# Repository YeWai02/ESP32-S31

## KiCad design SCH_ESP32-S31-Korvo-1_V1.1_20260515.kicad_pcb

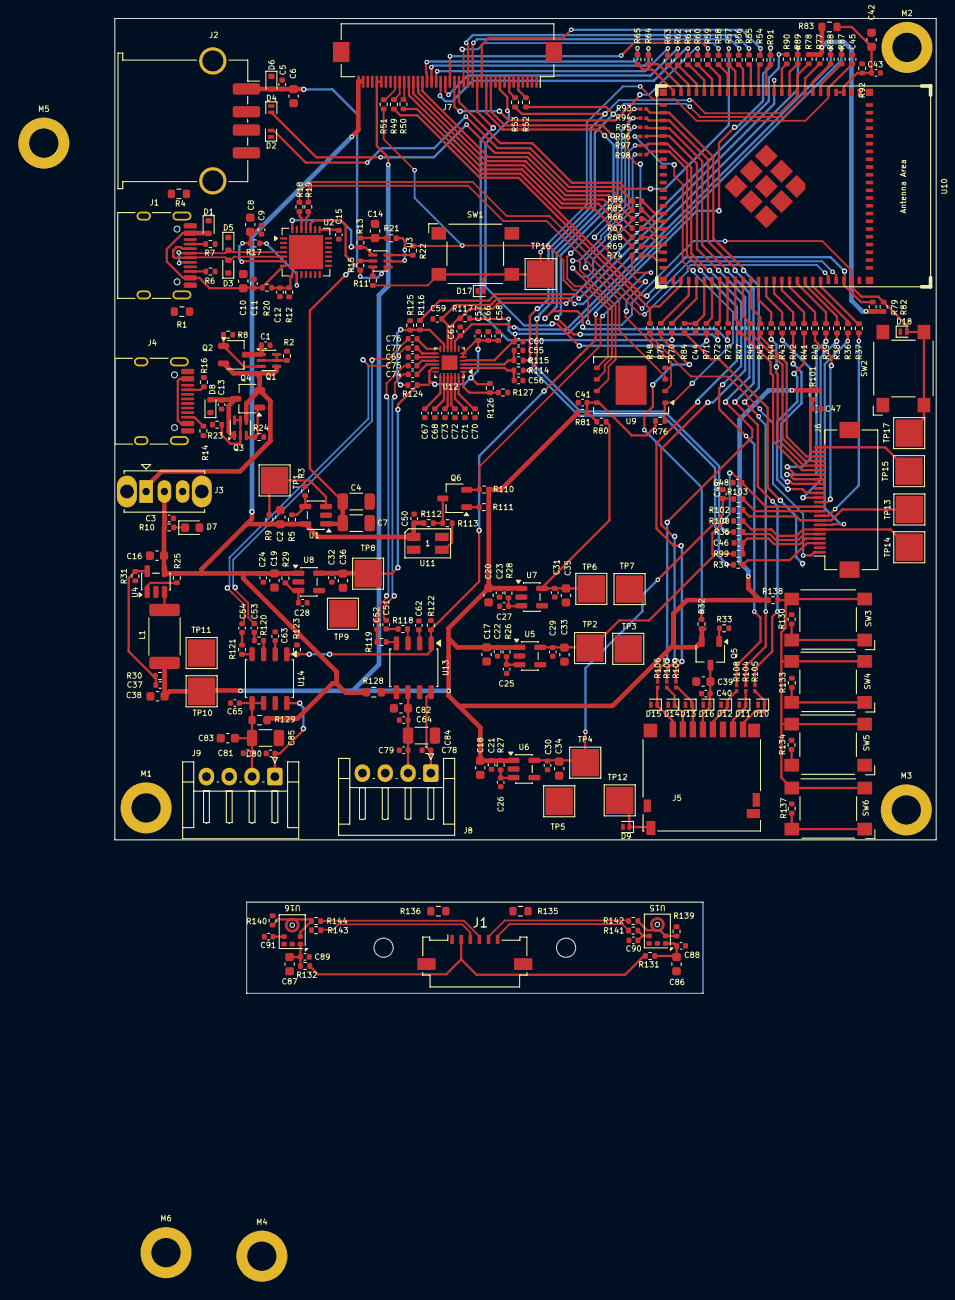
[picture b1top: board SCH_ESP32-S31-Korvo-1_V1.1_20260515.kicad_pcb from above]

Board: 2 copper layers, 90.0 x 90.0 mm, 315 parts (0 on the bottom side), 228 nets.

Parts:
C1, C13, C45, C57, C58, C62, C63, C64, C65, C66, C67, C68, C69, C70, C71, C72, C73, C74, C75, C76, C77: 1uF/16V(10%); C_0402_1005Metric
C2, C6, C8, C10, C16, C17, C18, C19, C33, C34, C36, C38, C39, C42, C86, C87: 10uF/10V(20%); C_0603_1608Metric
C3, C5, C9, C11, C12, C21, C22, C24, C29, C30, C32, C40, C43, C44, C47, C48, C49, C50, C51, C52, C53, C54, C88, C89: 0.1uF/10V(10%); C_0402_1005Metric
C4, C7, C84, C85: 100uF/10V(20%); C_1206_3216Metric
C14, C82, C83: NC; C_0603_1608Metric
C15, C23, C25, C26, C27, C28, C31, C41: 0.1uF/10V(10%)(NC); C_0402_1005Metric
C20, C35: 10uF/10V(20%)(NC); C_0603_1608Metric
C37: 22pF/50V(5%)(NC); C_0402_1005Metric
C46: 4.7uF/10V(10%); C_0402_1005Metric
C55, C56: 33pF/50V(5%); C_0402_1005Metric
C59, C60, C61, C90, C91: 22pF/50V(5%); C_0402_1005Metric
C78, C79, C80, C81: 1nF/50V(10%); C_0402_1005Metric
D1, D3, D5, D6, D8: LESD5D5.0CT1G; D_SOD-523
D2, D4: ESD7951ST5G; D_SOD-882
D7: LED-RED; LED_0603_1608Metric
D9, D10, D11, D12, D13, D14, D15, D16: BSDFN2C031U; D_SOD-882
D17, D18: LESD8D3.3CAT5G; D_SOD-882
J1: Molex_200528-0060_1x06-1MP_P1.00mm_Horizontal
J1#2, J4: USB_C_Receptacle_USB2.0_16P; USB_C_Receptacle_HRO_TYPE-C-31-M-12
J2: USB_A; USB_A_TE_292303-7_Horizontal
J3: CK_OS102011MS2Q; SW_Slide_SPDT_Straight_CK_OS102011MS2Q
J5: Micro_SD_Card_Det2; microSD_HC_Hirose_DM3D-SF
J6: FPC_24P_CAM; Hirose_FH12-24S-0.5SH_1x24-1MP_P0.50mm_Horizontal
J7: CON20X2_DIP_MALE; Hirose_FH12-40S-0.5SH_1x40-1MP_P0.50mm_Horizontal
J8, J9: PH2.0_2P; JST_EH_S4B-EH_1x04_P2.50mm_Horizontal
L1: 2.2uH(20%)_2A; L_2512_6332Metric
M1, M2, M3, M4, M5, M6: MountingHole-M3; MountingHole_3.2mm_M3_DIN965_Pad
Q1, Q3: LMBT3906DW1T1G; SOT-363_SC-70-6
Q2, Q4, Q5: AO3401A; TSOT-23
Q6: LBSS138LT1G; TSOT-23
R1, R4, R83, R128, R129, R135, R136: 0(1%); R_0603_1608Metric
R2, R5, R9, R13, R15, R23, R25, R26, R27, R29, R33, R92, R100, R102, R110, R122, R123, R138: 10K(1%); R_0402_1005Metric
R3, R28, R32, R76, R79, R82: 10K(1%)(NC); R_0402_1005Metric
R6, R7, R14, R16: 5.1K(1%); R_0402_1005Metric
R8, R24: 51K(1%); R_0402_1005Metric
R10: 2.2K(1%); R_0402_1005Metric
R11, R19, R21, R22, R34, R35, R36, R37, R38, R39, R40, R41, R42, R43, R44, R45, R46, R47, R49, R50, R51, R52, R53, R54, R55, R56, R57, R58, R59, R60, R61, R62, R63, R64, R65, R66, R67, R68, R69, R70, R71, R72, R73, R74, R75, R84, R85, R86, R87, R88, R89, R90, R91, R99, R101, R103, R111, R113, R116, R117, R131, R132, R139, R140, R141, R142, R143, R144: 0(1%); R_0402_1005Metric
R12: 47.5K(1%); R_0402_1005Metric
R17, R112: 1K(1%); R_0402_1005Metric
R18: 470(1%); R_0402_1005Metric
R20, R31: 22.1K(1%); R_0402_1005Metric
R30, R118, R119, R120, R121, R125, R127: 100K(1%); R_0402_1005Metric
R48, R80, R81: 0(1%)(NC); R_0402_1005Metric
R77, R78: 4.7K(1%); R_0402_1005Metric
R93, R94, R95, R96, R97, R98: 0(1%)(NC); R_0201_0603Metric
R104, R105, R106, R107, R108, R109: 0(1%); R_0201_0603Metric
R114, R115: 33(1%); R_0402_1005Metric
R124, R126: 100K(1%)(NC); R_0402_1005Metric
R130: 13K(1%); R_0402_1005Metric
R133: 6.8K(1%); R_0402_1005Metric
R134: 3.3K(1%); R_0402_1005Metric
R137: 1.3K(1%); R_0402_1005Metric
SW1, SW2, SW3, SW4, SW5, SW6: SW_Omron_B3FS; SW_SPST_Omron_B3FS-100xP
TP1, TP2, TP3, TP4, TP5, TP6, TP7, TP8, TP9, TP10, TP11, TP12, TP13, TP14, TP15, TP16, TP17: TESTPOINT; TestPoint_Pad_3.0x3.0mm
U1: TPS2051CDBVR; SOT-23-5
U2: CP2102N; QFN-28-1EP_5x5mm_P0.5mm_EP3.75x3.75mm
U3: BC847BDW1T1G; SOT-363_SC-70-6
U4: TLV62569; SOT-23-5
U5: ME6211C28M5G-N; SOT-23-5
U6: ME6211C15M5G-N; SOT-23-5
U7: ME6211C18M5G-N(NC); SOT-23-5
U8: ME6211C33M5G-N; SOT-23-5
U9: NAND_FLASH(NC); WSON-8-1EP_8x6mm_P1.27mm_EP3.4x4.3mm
U10: ESP32-S31-WROOM-3
U11: WS2812B; LED_RGB_Wuerth-PLCC4_3.2x2.8mm_150141M173100
U12: ES8389; QFN-24-1EP_3x3mm_P0.4mm_EP1.75x1.6mm
U13, U14: NS4150; SSOP-8_3.9x5.05mm_P1.27mm
U15, U16: LMA3729T381-OY3S; Knowles_SPH0645LM4H-6_3.5x2.65mm

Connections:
/AD0: R126.1, R127.1, U12.1 (AD0/DMIC_SCL)
/AD1: R116.2, R124.1, R125.1, U12.11 (ASDOUT/AD1)
/CAM_I2C_SCL: J6.5 (SCL), R35.1
/CAM_I2C_SDA: J6.3 (SDA), R34.1
/CAM_PWDN: J6.8 (PWDN), R102.2, TP13.1 (1_1)
/CAM_RESET: J6.6 (RESET), R100.1, TP14.1 (1_1)
/DTR: R13.1, U2.28 (DTR), U3.1 (E2)
/DVP_HREF: J6.9 (HREF), R37.1
/DVP_PCLK: J6.17 (PCLK), R39.1
/DVP_VSYNC: J6.7 (VSYNC), R36.1
/DVP_Y2: J6.19 (Y2), R47.1
/DVP_Y3: J6.21 (Y3), R46.1
/DVP_Y4: J6.22 (Y4), R45.1
/DVP_Y5: J6.20 (Y5), R44.1
/DVP_Y6: J6.18 (Y6), R43.1
/DVP_Y7: J6.16 (Y7), R42.1
/DVP_Y8: J6.14 (Y8), R41.1
/DVP_Y9: J6.12 (Y9), R40.1
/ES_LOUTN: C52.1, C75.2
/ES_LOUTP: C51.1, C74.2
/ES_MIC1N: C71.2, J1.5, R142.2
/ES_MIC1P: C70.2, J1.6, R141.2
/ES_MIC2N: C73.2, J1.4, R144.2
/ES_MIC2P: C72.2, J1.3, R143.2
/ES_ROUTN: C54.1, C77.2
/ES_ROUTP: C53.1, C76.2
/GM_FK: J6.1 (GM_FK), R48.1
/GPIO2: R87.2, U10.6 (GPIO2)
/GPIO3: R88.2, U10.7 (GPIO3)
/GPIO4: R89.2, U10.10 (GPIO4)
/GPIO5: R90.2, U10.11 (GPIO5)
/GPIO7: R91.2, U10.13 (GPIO7)
/GPIO8: R54.2, U10.14 (GPIO8)
/GPIO9: R55.2, U10.15 (GPIO9)
/GPIO10: R56.2, U10.16 (GPIO10)
/GPIO11: R57.2, U10.17 (GPIO11)
/GPIO12: R58.2, U10.18 (GPIO12)
/GPIO13: R59.2, U10.19 (GPIO13)
/GPIO14: R60.2, U10.20 (GPIO14)
/GPIO15: R61.2, U10.21 (GPIO15)
/GPIO16: R62.2, U10.22 (GPIO16)
/GPIO17: R63.2, U10.23 (GPIO17)
/GPIO18: R64.2, U10.24 (GPIO18)
/GPIO19: R65.2, U10.25 (GPIO19)
/GPIO20: R93.2, R104.1, U10.27 (SDIO_DATA0/GPIO20)
/GPIO21: R94.2, R105.1, U10.28 (SDIO_DATA1/GPIO21)
/GPIO22: R95.2, R106.1, U10.29 (SDIO_DATA2/GPIO22)
/GPIO23: R96.2, R107.1, U10.30 (SDIO_DATA3/GPIO23)
/GPIO24: R97.2, R108.1, U10.31 (SDIO_CLK/GPIO24)
/GPIO25: R98.2, R109.1, U10.32 (SDIO_CMD/GPIO25)
/GPIO33: R66.2, U10.42 (GPIO33)
/GPIO34: R67.2, U10.43 (GPIO34)
/GPIO35: R68.2, U10.44 (GPIO35)
/GPIO36: R69.2, U10.45 (GPIO36*)
/GPIO37: R74.2, U10.46 (GPIO37)
/GPIO38: R48.2, R49.2, U10.49 (GPIO38)
/GPIO39: R75.2, U10.50 (GPIO39)
/GPIO40: R70.2, U10.51 (GPIO40)
/GPIO42: C44.1, R84.2, U10.52 (GPIO42/ADC1_CH0_N)
/GPIO43: R71.2, U10.53 (GPIO43/ADC1_CH0_P)
/GPIO44: R72.2, U10.54 (GPIO44/ADC1_CH1_N)
/GPIO45: R73.2, U10.55 (GPIO45/ADC1_CH1_P)
/GPIO46: R47.2, U10.56 (GPIO46/ADC1_CH2_N)
/GPIO47: R46.2, U10.57 (GPIO47/ADC1_CH2_P)
/GPIO48: R45.2, U10.58 (GPIO48/ADC1_CH3_N)
/GPIO49: R44.2, U10.59 (GPIO49/ADC1_CH3_P)
/GPIO50: R43.2, U10.60 (GPIO50/ADC2_CH0_N)
/GPIO51: R42.2, U10.61 (GPIO51/ADC2_CH0_P)
/GPIO52: R41.2, U10.62 (GPIO52/ADC2_CH1_N)
/GPIO53: R40.2, U10.63 (GPIO53/ADC2_CH1_P)
/GPIO54: R39.2, U10.64 (MTDO/GPIO54)
/GPIO55: R38.2, U10.65 (MTCK/GPIO55)
/GPIO56: R36.2, U10.66 (MTDI/GPIO56)
/GPIO57: R37.2, U10.67 (MTMS/GPIO57)
/GPIO60: R50.2, R79.2, U10.70 (GPIO60)
/IR_CUT: J6.24 (IR_CUT), TP15.1 (1_1)
/LCD_B3: J7.13, R54.1
/LCD_B4: J7.16, R55.1
/LCD_B5: J7.15, R56.1
/LCD_B6: J7.18, R57.1
/LCD_B7: J7.17, R58.1
/LCD_CS: J7.31, R49.1
/LCD_G2: J7.20, R59.1
/LCD_G3: J7.19, R60.1
/LCD_G4: J7.22, R61.1
/LCD_G5: J7.21, R62.1
/LCD_G6: J7.23, R63.1
/LCD_G7: J7.24, R64.1
/LCD_H_EN: J7.9, R71.1
/LCD_H_SYNC: J7.11, R72.1
/LCD_I2C_SCL: J7.7, R53.1
/LCD_I2C_SDA: J7.5, R52.1
/LCD_MOSI: J7.30, R50.1
/LCD_PCLK: J7.14, R70.1
/LCD_R3: J7.25, R65.1
/LCD_R4: J7.26, R66.1
/LCD_R5: J7.27, R67.1
/LCD_R6: J7.28, R68.1
/LCD_R7: J7.29, R69.1
/LCD_SCK: J7.32, R51.1
/LCD_V_SYNC: J7.12, R73.1
/L_INL+: R118.2, U13.3 (IN+)
/L_INL-: R119.2, U13.4 (IN-)
/L_OUTL+: C78.1, J8.1, U13.8 (OUT+)
/L_OUTL-: C64.1, C79.1, C82.2, C84.1, J8.2, R128.1, U13.5 (OUT-), U13.6 (VCC)
/NAND_FLASH_CK: R93.1, U9.6 (CLK)
/NAND_FLASH_CS: R76.1, R96.1, U9.1 (/CS)
/NAND_FLASH_D: R94.1, U9.5 (DI)
/NAND_FLASH_HD: R97.1, U9.7 (/HOLD)
/NAND_FLASH_Q: R95.1, U9.2 (DO)
/NAND_FLASH_WP: R98.1, U9.3 (/WP)
/RTS: R15.2, U2.24 (RTS), U3.4 (E1)
/R_INL+: R120.2, U14.3 (IN+)
/R_INL-: R121.2, U14.4 (IN-)
/R_OUTL+: C80.1, J9.1, U14.8 (OUT+)
/R_OUTL-: C65.1, C81.1, C83.2, C85.1, J9.2, R129.1, U14.5 (OUT-), U14.6 (VCC)
/SD_CLK: D12.1, J5.5 (CLK), R108.2
/SD_CMD: D13.1, J5.3 (CMD), R109.2
/SD_CTRL: R32.1, R75.1
/SD_D0: D11.1, J5.7 (DAT0), R104.2
/SD_D1: D10.1, J5.8 (DAT1), R105.2
/SD_D2: D15.1, J5.1 (DAT2), R106.2
/SD_D3: D14.1, J5.2 (DAT3/CD), R107.2
/SD_DET: D9.1, J5.10 (DET_A), TP12.1 (1_1)
/USB_D+: D5.2, J1#2.A6 (D+), J1#2.B6 (D+), U2.4 (D+)
/USB_D-: D3.2, J1#2.A7 (D-), J1#2.B7 (D-), U2.5 (D-)
/USB_DM-: R85.2, U10.41 (USB_DM)
/USB_DP+: R86.2, U10.40 (USB_DP)
/VBUS_EN: R3.2, R5.2, U1.4 (EN)
/WS2812_CTRL: Q6.2 (S), R74.1, R110.2
/WS2812_DIN: R113.2, U11.2 (DIN)
/XMCLK: J6.13 (XCLK), R38.1
AGND: C55.1, C56.1, C57.1, C58.1, C59.2, C60.2, C61.2, C66.2, C67.2, C68.2, C69.2, C86.2, C87.2, C88.2, C89.2, C90.2, C91.2, J1.1, J1.7, J1.8, R125.2, R127.2, R135.1, R136.1, R139.1, R140.1, U12.7 (DGND), U12.18 (AGND), U12.25 (PGND)
AVDD_2V8: C46.1, J6.4 (AVDD), R99.1
Aud_3V3: C32.1, C36.1, C57.2, C58.2, C66.1, J1.2, R124.2, R126.2, R131.1, R132.1, TP8.1 (1_1), U8.5 (OUT), U12.5 (DVDD), U12.6 (PVDD), U12.17 (AVDD)
BT_ARRAY_ADC: R84.1, R138.2, SW3.2, SW4.2, SW5.2, SW6.2
DOVDD_2V8: C29.1, C33.1, C48.1, J6.11 (DOVDD), R99.2, R100.2, TP2.1 (1_1), U5.5 (OUT)
DVDD_1V5: C30.1, C34.1, C49.1, R103.1, TP4.1 (1_1), U6.5 (OUT)
EN: C45.1, D17.2, R11.1, R92.2, SW1.2, TP16.1 (1_1), U10.5 (EN)
ESP_3V3: C42.1, C43.1, R83.2, R92.1, U10.3 (3V3), U10.4 (3V3)
GND: C1.2, C2.2, C3.2, C4.2, C5.2, C6.2, C7.2, C8.2, C9.2, C10.2, C11.2, C12.2, C13.2, C14.2, C15.2, C16.2, C17.2, C18.2, C19.2, C20.2, C21.2, C22.2, C23.2, C24.2, C25.2, C26.2, C27.2, C28.2, C29.2, C30.2, C31.2, C32.2, C33.2, C34.2, C35.2, C36.2, C38.2, C39.2, C40.2, C41.2, C42.2, C43.2, C44.2, C45.2, C46.2, C47.2, C48.2, C49.2, C50.2, C62.2, C63.2, C64.2, C65.2, C78.2, C79.2, C80.2, C81.2, C82.1, C83.1, C84.2, C85.2, D1.1, D2.1, D3.1, D4.1, D5.1, D6.1, D7.2 (CATHODE), D8.1, D9.2, D10.2, D11.2, D12.2, D13.2, D14.2, D15.2, D16.2, D17.1, D18.1, J1#2.A1 (GND), J1#2.A12 (GND), J1#2.B1 (GND), J1#2.B12 (GND), J2.4 (GND), J3.3 (C), J4.A1 (GND), J4.A12 (GND), J4.B1 (GND), J4.B12 (GND), J5.6 (VSS), J5.9 (DET_B), J5.SH (SHIELD), J6.2 (AGND), J6.15 (DGND), J6.MP (NC2), J7.1, J7.2, J7.8, J7.33, J7.34, J7.37, J7.38, J7.MP (NC1), J8.3, J8.4, J9.3, J9.4, R1.1, R2.2, R3.1, R4.2, R6.1, R7.1, R8.2, R12.2, R14.1, R16.1, R23.2, R24.2, R31.2, R33.2, R102.1, R122.2, R123.2, R130.1, R133.1, R134.1, R135.2, R136.2, R137.1, SW1.1, SW2.1, TP3.1 (1_1), TP5.1 (1_1), TP7.1 (1_1), TP9.1 (1_1), TP11.1 (1_1), U1.2 (GND), U2.3 (GND), U2.29 (PGND), U4.2 (GND), U5.2 (GND), U6.2 (GND), U7.2 (GND), U8.2 (GND), U9.4 (GND), U9.9 (EPAD), U10.1 (GND), U10.2 (GND), U10.26 (GND), U10.47 (GND), U10.48 (GND), U10.72 (GND), U10.73 (GND), U10.74 (GND), U10.75 (GND), U10.76 (GND), U10.77 (GND), U10.78 (GND), U10.79 (GND), U10.80 (GND), U10.81 (GND), U10.82 (GND), U10.83 (GND), U10.84 (GND), U10.85 (GND), U10.86 (GND), U10.87 (GND), U10.88 (GND), U10.89 (GND), U10.90 (GND), U10.92 (GND), U10.93 (GND), U10.94 (GND), U10.95 (GND), U10.96 (GND), U10.97 (GND), U10.98 (GND), U10.99 (GND), U11.1 (VSS), U13.7 (GND), U14.7 (GND)
GND_EARTH: J1#2.SH (SHIELD), J4.SH (SHIELD), R1.2
GND_EARTH1: J2.SH (Shield), R4.1
GPIO0: R34.2, R52.2, R77.2, R114.1, U10.8 (GPIO0/XTAL_32K_N)
GPIO1: R35.2, R53.2, R78.2, R115.1, U10.9 (GPIO1/XTAL_32K_P)
GPIO61: D18.2, R22.2, R51.2, R82.2, SW2.2, TP17.1 (1_1), U10.71 (GPIO61)
I2S_DSDIN: R90.1, R117.1, U12.9 (DSDIN)
I2S_LRCK: C59.1, R89.1, U12.10 (LRCK)
I2S_MCLK: C60.1, R87.1, R117.2, U12.4 (MCLK/DMIC_SCL/TDMIN)
I2S_SCLK: C61.1, R88.1, U12.8 (SCLK)
I2S_SDOUT: R116.1, U10.12 (GPIO6)
unnamed: C14.1, R13.2, R21.1
unnamed: C51.2, R118.1
unnamed: C52.2, R119.1
unnamed: C53.2, R120.1
unnamed: C54.2, R121.1
unnamed: D7.1 (ANODE), R10.1
unnamed: J1#2.A5 (CC1), R7.2
unnamed: J1#2.B5 (CC2), R6.2
unnamed: J4.A5 (CC1), R16.2
unnamed: J4.B5 (CC2), R14.2
unnamed: J4.A4 (VBUS), J4.A9 (VBUS), J4.B4 (VBUS), J4.B9 (VBUS)
unnamed: J6.10 (DVDD), R103.2
unnamed: C47.1, J6.23 (LED+), R101.2
unnamed: Q1.2, Q1.5, Q1.6, R2.1
unnamed: Q1.3, Q2.1 (G), R8.1
unnamed: Q3.2, Q3.5, Q3.6, R23.1
unnamed: Q3.3, Q4.1 (G), R24.1
unnamed: Q5.1 (G), R33.1
unnamed: Q6.3 (D), R112.1, R113.1
unnamed: Q6.1 (G), R111.1
unnamed: R130.2, SW3.1
unnamed: R133.2, SW4.1
unnamed: R134.2, SW5.1
unnamed: R137.2, SW6.1
unnamed: R9.2, TP1.1 (1_1), U1.3 (FLG)
unnamed: C15.1, U2.22 (NC11)
unnamed: R19.1, U2.25 (RXD)
unnamed: R18.1, U2.26 (TXD)
unnamed: C12.1, R12.1, R20.2, U2.8 (VBUS)
unnamed: R17.1, U2.9 (~RST)
unnamed: R21.2, U3.5 (B1)
unnamed: R15.1, U3.2 (B2)
unnamed: R11.2, U3.3 (C1)
unnamed: R22.1, U3.6 (C2)
unnamed: R25.2, U4.1 (EN/PG)
unnamed: C37.2, R30.2, R31.1, U4.5 (FB)
unnamed: L1.1, U4.3 (SW)
unnamed: C25.1, R26.1, U5.3 (EN)
unnamed: C26.1, R27.1, U6.3 (EN)
unnamed: C27.1, R28.1, U7.3 (EN)
unnamed: C28.1, R29.1, U8.3 (EN)
unnamed: C41.1, R76.2, R80.1, R81.1, U9.8 (VCC)
unnamed: C68.1, U12.20 (ADCVREF)
unnamed: C55.2, R115.2, U12.3 (CCLK)
unnamed: C56.2, R114.2, U12.2 (CDATA)
unnamed: C69.1, U12.14 (DACVREF)
unnamed: C75.1, U12.15 (LOUTN)
unnamed: C74.1, U12.16 (LOUTP)
unnamed: C71.1, U12.23 (MIC1N/DMIC_SCL)
unnamed: C70.1, U12.24 (MIC1P/DMIC_SDA)
unnamed: C73.1, U12.21 (MIC2N)
unnamed: C72.1, U12.22 (MIC2P)
unnamed: C77.1, U12.13 (ROUTN)
unnamed: C76.1, U12.12 (ROUTP)
unnamed: C67.1, U12.19 (VMID)
unnamed: C62.1, U13.2 (Bypass)
unnamed: C63.1, U14.2 (Bypass)
unnamed: R139.2, R142.1, U15.2 (GND1), U15.3 (GND2)
unnamed: C90.1, R141.1, U15.4 (OUT)
unnamed: C86.1, C88.1, R131.2, U15.1 (VDD)
unnamed: R140.2, R144.1, U16.2 (GND1), U16.3 (GND2)
unnamed: C91.1, R143.1, U16.4 (OUT)
unnamed: C87.1, C89.1, R132.2, U16.1 (VDD)
PA_CTRL: R91.1, R122.1, R123.1, U13.1 (CTRL), U14.1 (CTRL)
RX0: R18.2, U10.69 (UART0_RXD/GPIO59)
SD_3V3: C39.1, C40.1, D16.1, J5.4 (VDD), Q5.3 (D)
TX0: R19.2, U10.68 (UART0_TXD/GPIO58)
USB0_5V: C1.1, C10.1, C11.1, D1.2, J1#2.A4 (VBUS), J1#2.A9 (VBUS), J1#2.B4 (VBUS), J1#2.B9 (VBUS), Q1.1 (1E), Q2.3 (D), R20.1, U2.7 (REGIN)
USB1_5V: C13.1, D8.2, Q3.1 (1E), Q4.3 (D)
USB_DM_A-: D4.2, J2.2 (D-), R85.1
USB_DP_A+: D2.2, J2.3 (D+), R86.1
VBUS_OUT: C4.1, C5.1, C6.1, C7.1, D6.2, J2.1 (VBUS), U1.1 (OUT)
VCC_1V8: C31.1, C35.1, R80.2, TP6.1 (1_1), U7.5 (OUT)
VCC_3V3: C17.1, C18.1, C20.1, C21.1, C22.1, C23.1, C37.1, C38.1, J7.35, J7.36, L1.2, Q5.2 (S), R26.2, R27.2, R28.2, R30.1, R32.2, R77.1, R78.1, R79.1, R81.2, R82.1, R83.1, R101.1, R110.1, R111.2, R138.1, TP10.1 (1_1), U5.1 (VIN), U6.1 (VIN), U7.1 (VIN)
VCC_5V: C2.1, C3.1, C16.1, C19.1, C24.1, C50.1, J3.2 (B), J7.39, J7.40, R5.1, R9.1, R10.2, R25.1, R29.2, R112.2, R128.2, R129.2, U1.5 (IN), U4.4 (VIN), U8.1 (VIN), U11.3 (VDD)
VCC_IN: J3.1 (A), Q1.4, Q2.2 (S), Q3.4, Q4.2 (S)
VDD: C8.1, C9.1, R17.2, U2.6 (VDD)
